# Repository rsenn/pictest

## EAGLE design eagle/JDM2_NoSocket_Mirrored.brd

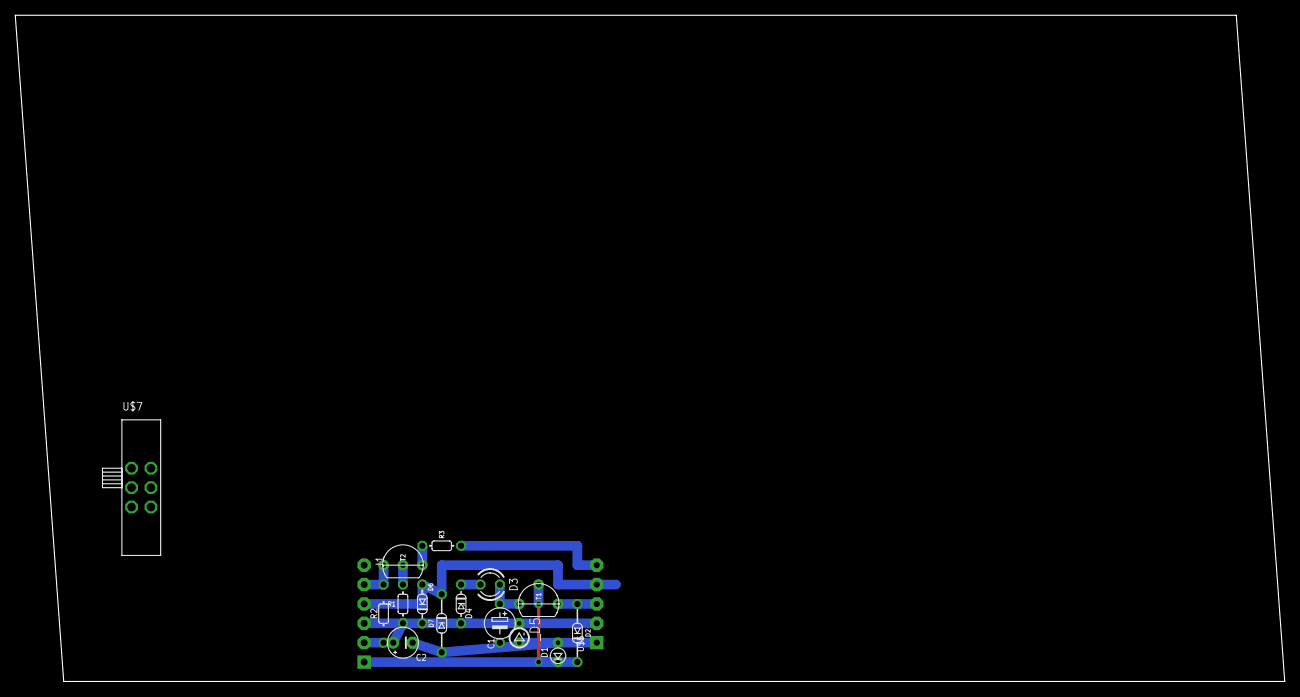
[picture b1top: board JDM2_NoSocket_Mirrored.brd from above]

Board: 2 copper layers, 166.3 x 87.3 mm, 17 parts (0 on the bottom side), 12 nets.

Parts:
C1: 100μF; E5-4
C2: 22μF; E2,5-4
D1: 1N4148; DO34-2,5-A
D2, D7: 1N4148; DO34-7
D3: Vpp; LED3MM
D4: Z=8.1V; DO34Z5
D6: 1N4148; DO34-5
J1: COMPORT-6PIN; RS232-6PIN
R1: 10kΩ; 0202/5
R2: 1.5kΩ; 0202/7
R3: 100Ω; 0202/5
T1: BC547CBE-A; TO92-CBE-A
T2: BC547CBE; TO92-CBE
U$5: PIC-ICSPICSP; PIC-ICSP
U$7: SL-SW-2P-2T-H; SLSW-2P2T-H
_D5: Z=5.1V; DO35Z2_54

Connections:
/MCLR: D2.A, T1.E, U$5.3
CLK: D6.A, D7.C, J1.4, U$5.4
CTS: J1.5, R2.2, T2.C
DATA: R3.2, T2.E
DTR: J1.2, R2.1
unnamed: R1.1, T2.B
unnamed: D3.K, D4.C
PGD: R3.1, U$5.5
TXD: D1.C, D2.C, J1.1, T1.B
VDD: C2.+, D4.A, D6.C, J1.3, R1.2, U$5.2, _D5.C
VPP: C1.+, D3.A, T1.C
VSS: C1.-, C2.-, D1.A, D7.A, U$5.1, _D5.A

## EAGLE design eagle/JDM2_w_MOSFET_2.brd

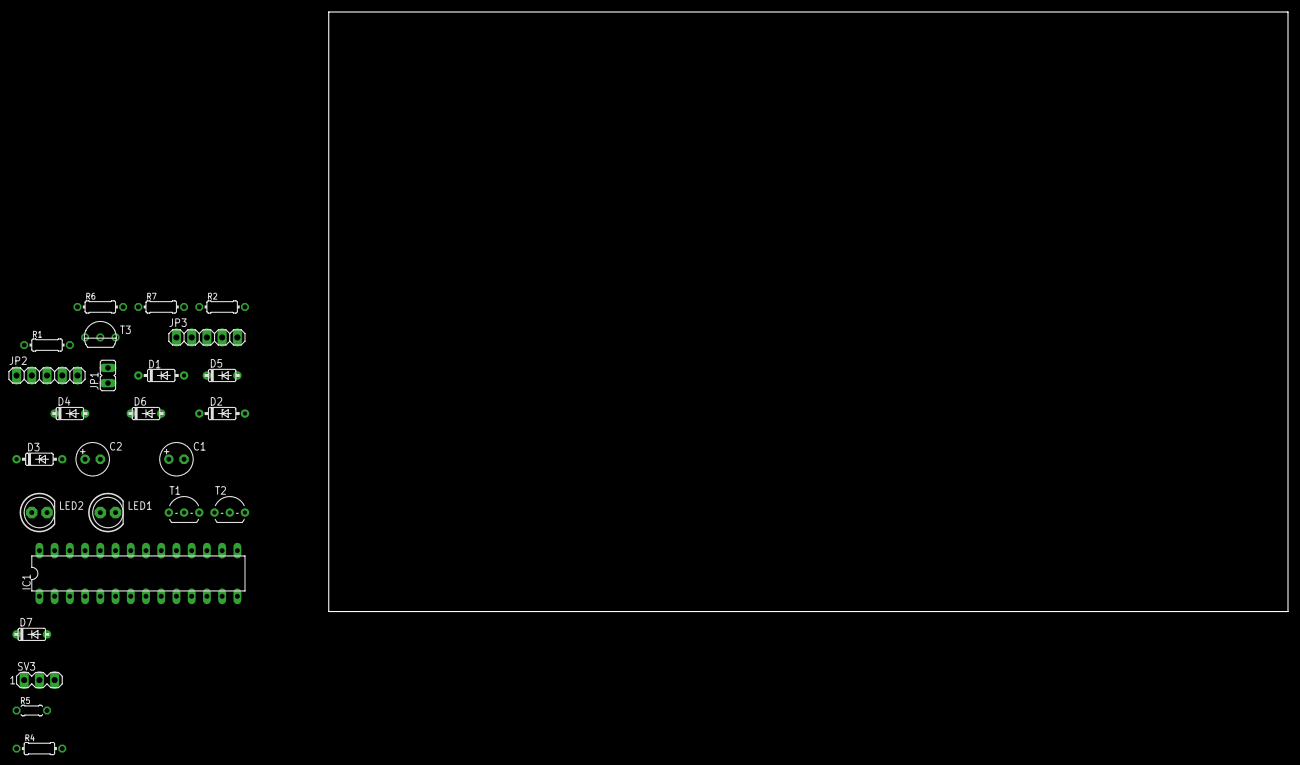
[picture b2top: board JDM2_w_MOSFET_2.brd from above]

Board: 2 copper layers, 160.0 x 100.0 mm, 25 parts (0 on the bottom side), 17 nets, no tracks yet.

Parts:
C1: 100uF 40v; E2,5-6
C2: 22uF 16v; E2,5-6
D1: 1N4148; DO35-7
D2: 8.2v; DO35Z7
D3: 5.1v; DO35Z7
D4, D5, D6: 1N4148; DO35-5
D7: 2N4148; DO35-5
IC1: DIL28-3
JP1: \!28p; JP1
JP2, JP3: 1X05
LED1: Power; LED5MM
LED2: Vpp; LED5MM
R1: 10k; 0204/7
R2: 1.5k; 0204/7
R4: 1K; 0204/7
R5: 15K; 0204/5
R6: 4.7k; 0204/7
R7: 1.2k; 0204/7
SV3: MA03-1
T1, T2: BC547; TO92-CBE
T3: 2N7000; TO92

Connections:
2N3904: C1.+, D2.C, T1.C
CTS: JP2.5, R2.2, T2.C
DATA: IC1.28, JP3.5, T2.E
DTR: JP2.2, R2.1
GND: C1.-, C2.-, D1.A, D3.A, D5.A, IC1.8, IC1.19, JP3.1, LED1.K, LED2.K, R5.1
MCLR: IC1.1, JP3.3, SV3.2
unnamed: R1.1, T2.B
unnamed: LED1.A, R7.1
unnamed: LED2.A, R6.1
unnamed: IC1.5, IC1.14, JP1.2
unnamed: R4.1, SV3.3
unnamed: D7.A, R4.2, R5.2
RTS: D4.A, D5.C, IC1.27, JP2.4, JP3.4
SGND: C2.+, D2.A, D3.C, D4.C, JP2.3, R7.2, T3.1
TXD: D1.C, D6.C, JP2.1, T1.B
VDD: IC1.20, IC1.25, JP3.2, R1.2, T3.3
VPP: D6.A, D7.C, JP1.1, R6.2, SV3.1, T1.E, T3.2

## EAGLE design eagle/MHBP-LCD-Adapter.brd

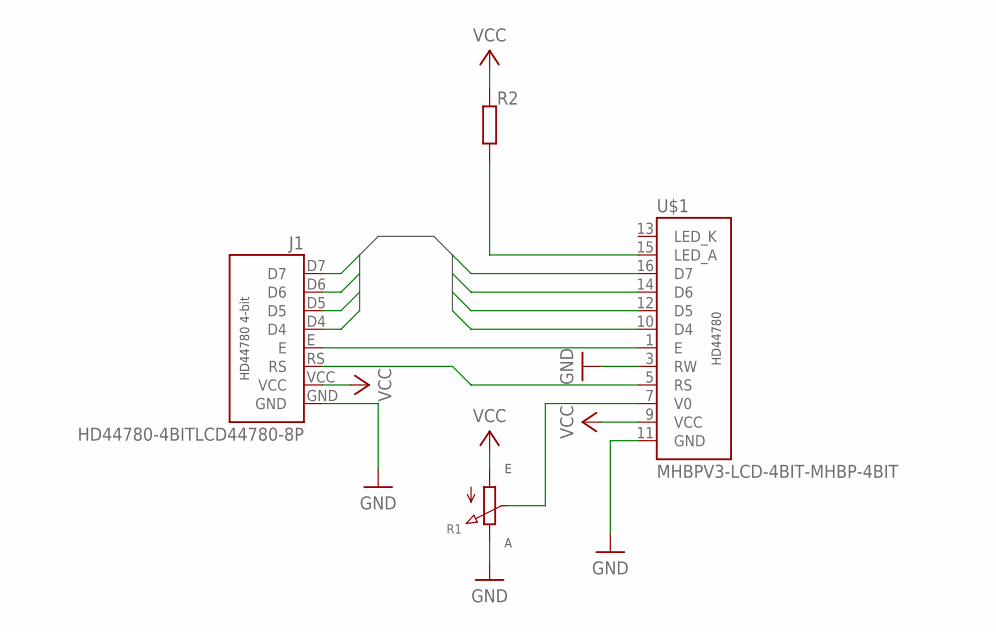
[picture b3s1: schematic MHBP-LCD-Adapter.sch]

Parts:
J1: HD44780-4BITLCD44780-8P; CONN-LCD44780
R1: POT-V
R2: R0207/12; 0207/12
U$1: MHBPV3-LCD-4BIT-MHBP-4BIT; MBHP-LCD-4BIT

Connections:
D4: J1.D4, U$1.10 (D4)
D5: J1.D5, U$1.12 (D5)
D6: J1.D6, U$1.14 (D6)
D7: J1.D7, U$1.16 (D7)
GND: J1.GND, R1.E, U$1.3 (RW), U$1.11 (GND)
unnamed: R1.S, U$1.7 (V0)
unnamed: J1.RS, U$1.5 (RS)
unnamed: J1.E, U$1.1 (E)
unnamed: R2.1, U$1.15 (LED_A)
VCC: J1.VCC, R1.A, R2.2, U$1.9 (VCC)

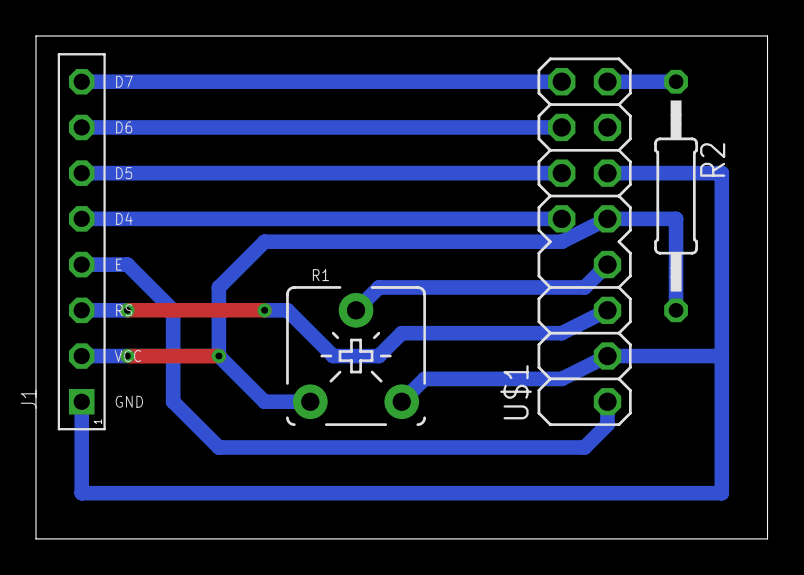
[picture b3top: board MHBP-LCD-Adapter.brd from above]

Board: 2 copper layers, 40.6 x 27.9 mm, 4 parts (0 on the bottom side), 10 nets.

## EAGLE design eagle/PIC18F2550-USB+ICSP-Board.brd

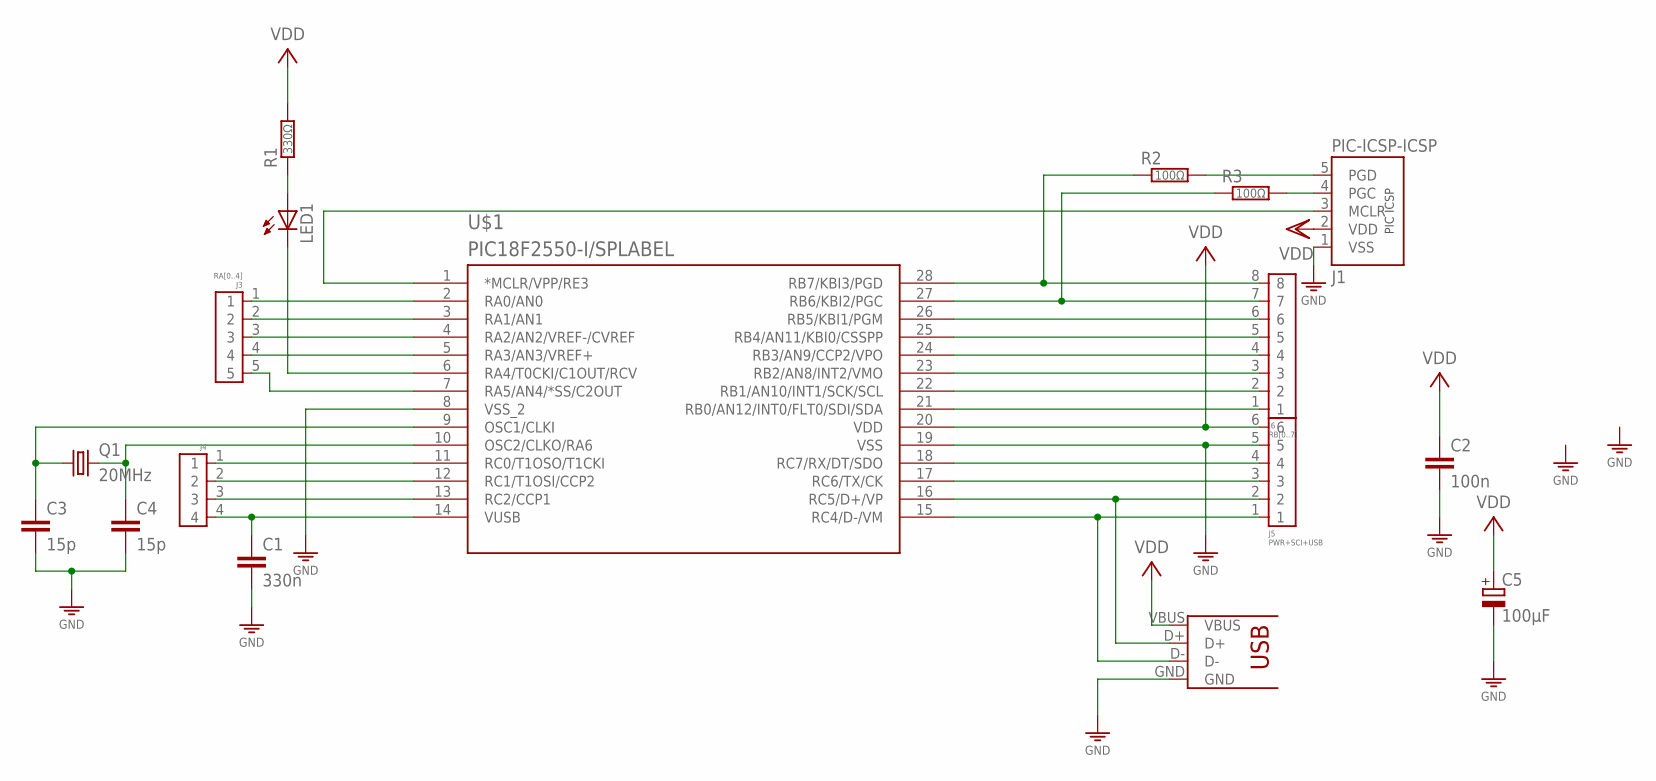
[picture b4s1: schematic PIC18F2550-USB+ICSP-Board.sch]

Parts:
C1: 330n; C050-030X075
C2: 100n; C025-015X024
C3, C4: 15p; C025-015X024
C5: 100μF; E2,5-5
J1: PIC-ICSP-ICSP; PIC-ICSP
J2: USB-PRINT; USB-B-PRINT
J3: RA[0..4]; CONN-5P-N
J4: RC[0..3]; CONN-4P
J5: PWR+SCI+USB; CONN-6P
J6: RB[0..7]; CONN-8P
LED1: LED5MM
Q1: 20MHz; HC49
R1: 330Ω; 0204/10
R2, R3: 100Ω; 0204/7-V
U$1: PIC18F2550-I/SPLABEL; PIC18F2550-V

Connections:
/MCLR: J1.3 (MCLR), U$1.1 (*MCLR/VPP/RE3)
GND: C1.2, C2.2, C3.2, C4.2, C5.-, J1.1 (VSS), J2.GND, J5.5, U$1.8 (VSS_2), U$1.19 (VSS)
unnamed: C1.1, J4.4, U$1.14 (VUSB)
unnamed: J2.D+, J5.2, U$1.16 (RC5/D+/VP)
unnamed: J2.D-, J5.1, U$1.15 (RC4/D-/VM)
unnamed: LED1.A, R1.1
unnamed: J3.5, U$1.7 (RA5/AN4/*SS/C2OUT)
unnamed: C3.1, Q1.1, U$1.9 (OSC1/CLKI)
unnamed: C4.1, Q1.2, U$1.10 (OSC2/CLKO/RA6)
unnamed: J6.6, U$1.26 (RB5/KBI1/PGM)
unnamed: J6.5, U$1.25 (RB4/AN11/KBI0/CSSPP)
unnamed: J6.4, U$1.24 (RB3/AN9/CCP2/VPO)
unnamed: J6.3, U$1.23 (RB2/AN8/INT2/VMO)
unnamed: J6.2, U$1.22 (RB1/AN10/INT1/SCK/SCL)
unnamed: J6.1, U$1.21 (RB0/AN12/INT0/FLT0/SDI/SDA)
unnamed: J3.1, U$1.2 (RA0/AN0)
unnamed: J5.4, U$1.18 (RC7/RX/DT/SDO)
unnamed: J5.3, U$1.17 (RC6/TX/CK)
unnamed: J3.2, U$1.3 (RA1/AN1)
unnamed: J3.3, U$1.4 (RA2/AN2/VREF-/CVREF)
unnamed: J3.4, U$1.5 (RA3/AN3/VREF+)
unnamed: LED1.K (C), U$1.6 (RA4/T0CKI/C1OUT/RCV)
unnamed: J4.1, U$1.11 (RC0/T1OSO/T1CKI)
unnamed: J4.2, U$1.12 (RC1/T1OSI/CCP2)
unnamed: J4.3, U$1.13 (RC2/CCP1)
unnamed: J1.5 (PGD), R2.2
unnamed: J1.4 (PGC), R3.2
PGC: J6.7, R3.1, U$1.27 (RB6/KBI2/PGC)
PGD: J6.8, R2.1, U$1.28 (RB7/KBI3/PGD)
VCC: C2.1, C5.+, J2.VBUS, J5.6, R1.2, U$1.20 (VDD)
VDD: J1.2 (VDD)

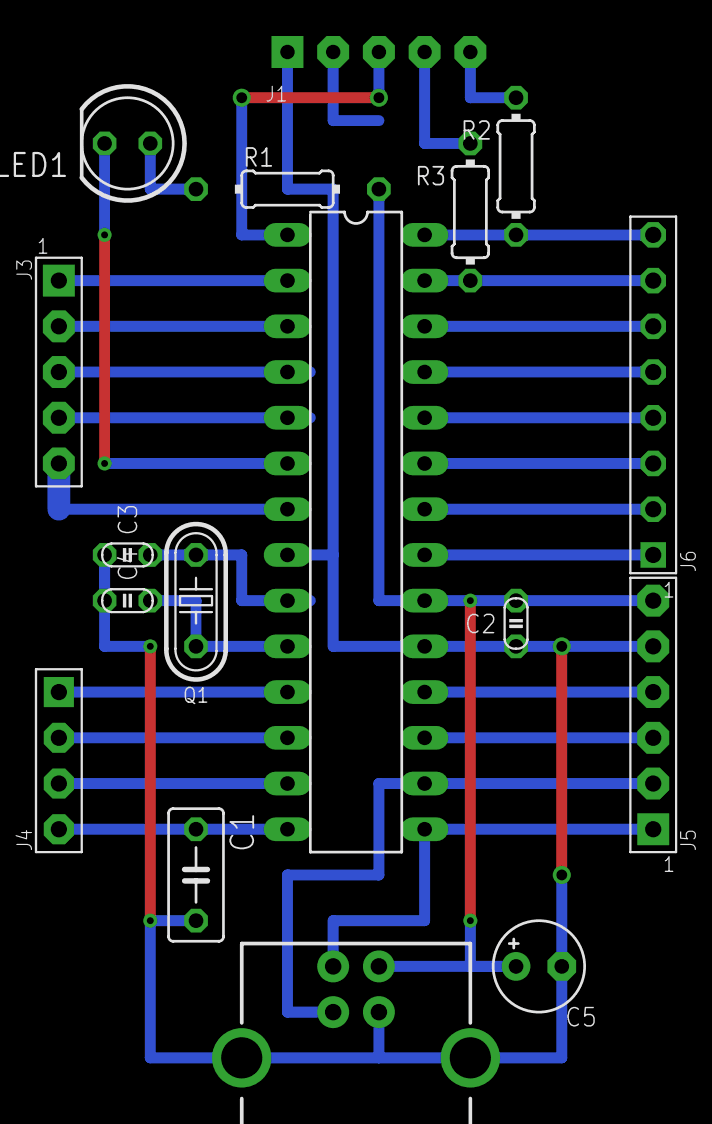
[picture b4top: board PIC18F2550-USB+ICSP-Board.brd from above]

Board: 2 copper layers, 17 parts (0 on the bottom side), 30 nets.
